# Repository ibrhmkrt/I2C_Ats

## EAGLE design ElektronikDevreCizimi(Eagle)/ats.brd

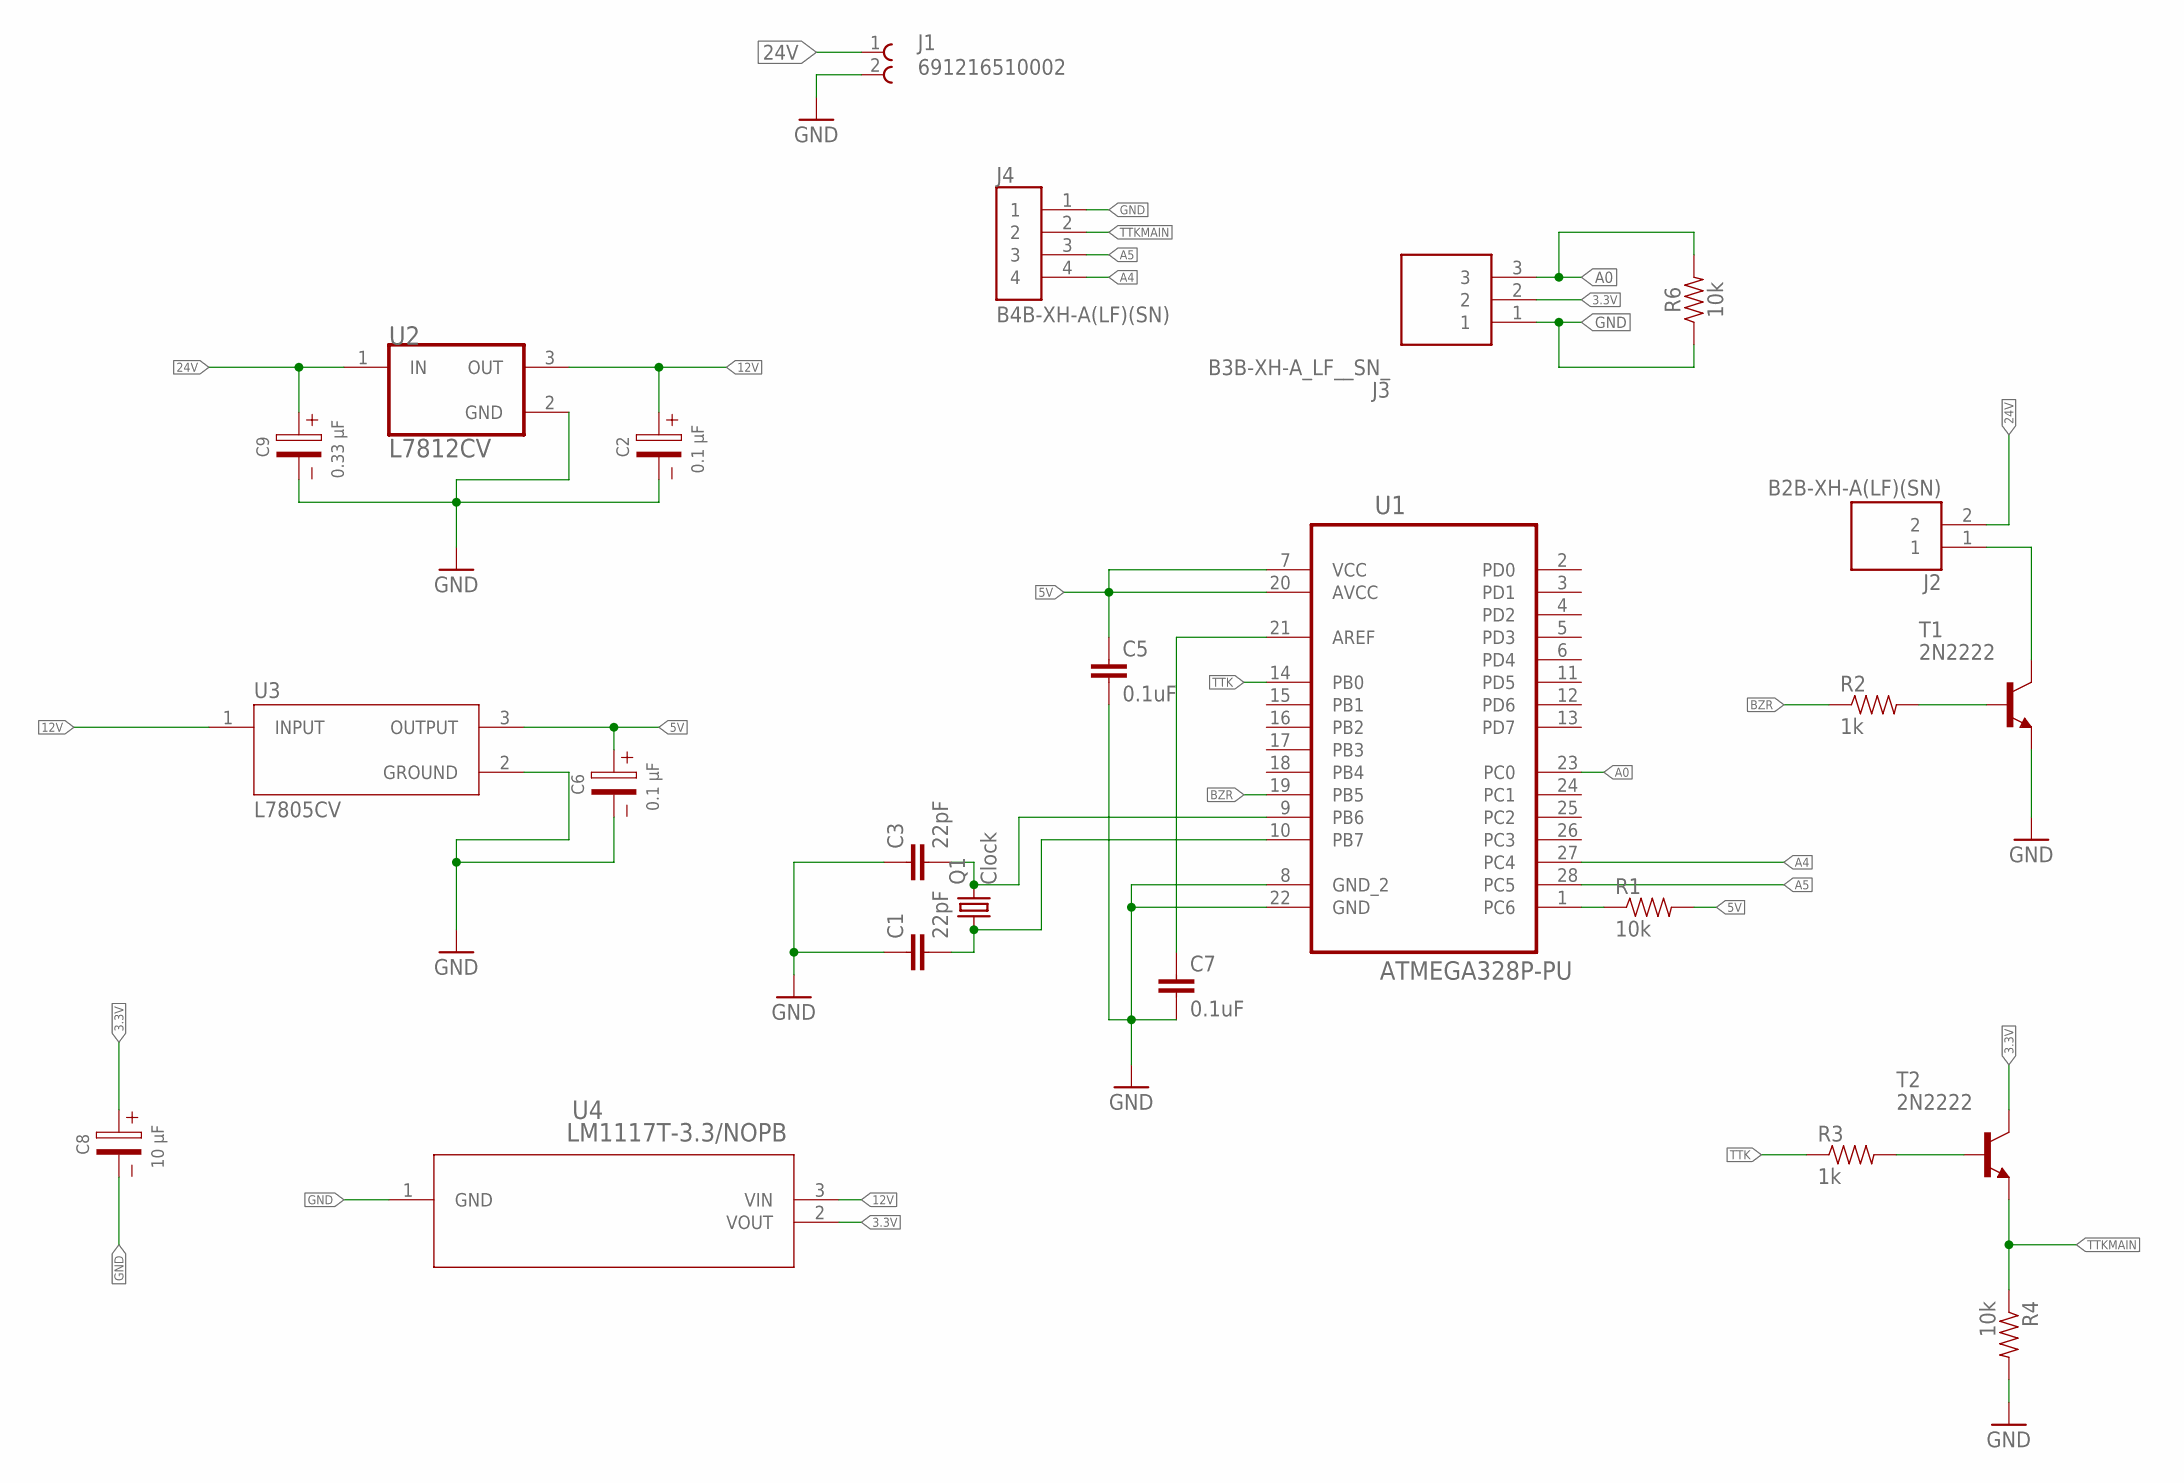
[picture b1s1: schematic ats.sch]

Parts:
C1, C3: 22pF; CAP-PTH-2.54
C2, C6: 0.1 µF; WCAP-ATG5_5X11(DXL)
C5, C7: 0.1uF; CAP-PTH-SMALL-KIT
C8: 10 µF; WCAP-ATG5_5X11(DXL)
C9: 0.33 µF; WCAP-ATG5_5X11(DXL)
J1: 691216510002
J2: B2B-XH-A(LF)(SN); JST_B2B-XH-A(LF)(SN)
J3: B3B-XH-A_LF__SN_; SHDR3W64P0X250_1X3_990X575X700
J4: B4B-XH-A(LF)(SN); JST_B4B-XH-A(LF)(SN)
Q1: Clock; HC49/S
R1, R4, R6: 10k; AXIAL-0.3
R2, R3: 1k; AXIAL-0.3
T1, T2: 2N2222; TO92-EBC-OVAL
U1: ATMEGA328P-PU; DIP254P762X457-28
U2: L7812CV; TO-220-3
U3: L7805CV; TO255P1040X460X1968-3
U4: LM1117T-3.3/NOPB; T03B_TEX

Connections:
3.3V: C8.1 (+), J3.2, T2.C, U4.2 (VOUT)
5V: C5.1, C6.1 (+), R1.P$2 (2), U1.7 (VCC), U1.20 (AVCC), U3.3 (OUTPUT)
12V: C2.1 (+), U2.3 (OUT), U3.1 (INPUT), U4.3 (VIN)
24V: C9.1 (+), J1.1, J2.2, U2.1 (IN)
A0: J3.3, R6.P$2 (2), U1.23 (PC0)
A4: J4.4, U1.27 (PC4)
A5: J4.3, U1.28 (PC5)
BZR: R2.P$1 (1), U1.19 (PB5)
GND: C1.1, C2.2 (-), C3.1, C5.2, C6.2 (-), C7.2, C8.2 (-), C9.2 (-), J1.2, J3.1, J4.1, R4.P$2 (2), R6.P$1 (1), T1.E, U1.8 (GND_2), U1.22 (GND), U2.2 (GND), U3.2 (GROUND), U4.1 (GND)
unnamed: R1.P$1 (1), U1.1 (PC6)
unnamed: J2.1, T1.C
unnamed: R2.P$2 (2), T1.B
unnamed: C3.2, Q1.2, U1.9 (PB6)
unnamed: C1.2, Q1.1, U1.10 (PB7)
unnamed: C7.1, U1.21 (AREF)
unnamed: R3.P$2 (2), T2.B
TTK: R3.P$1 (1), U1.14 (PB0)
TTKMAIN: J4.2, R4.P$1 (1), T2.E

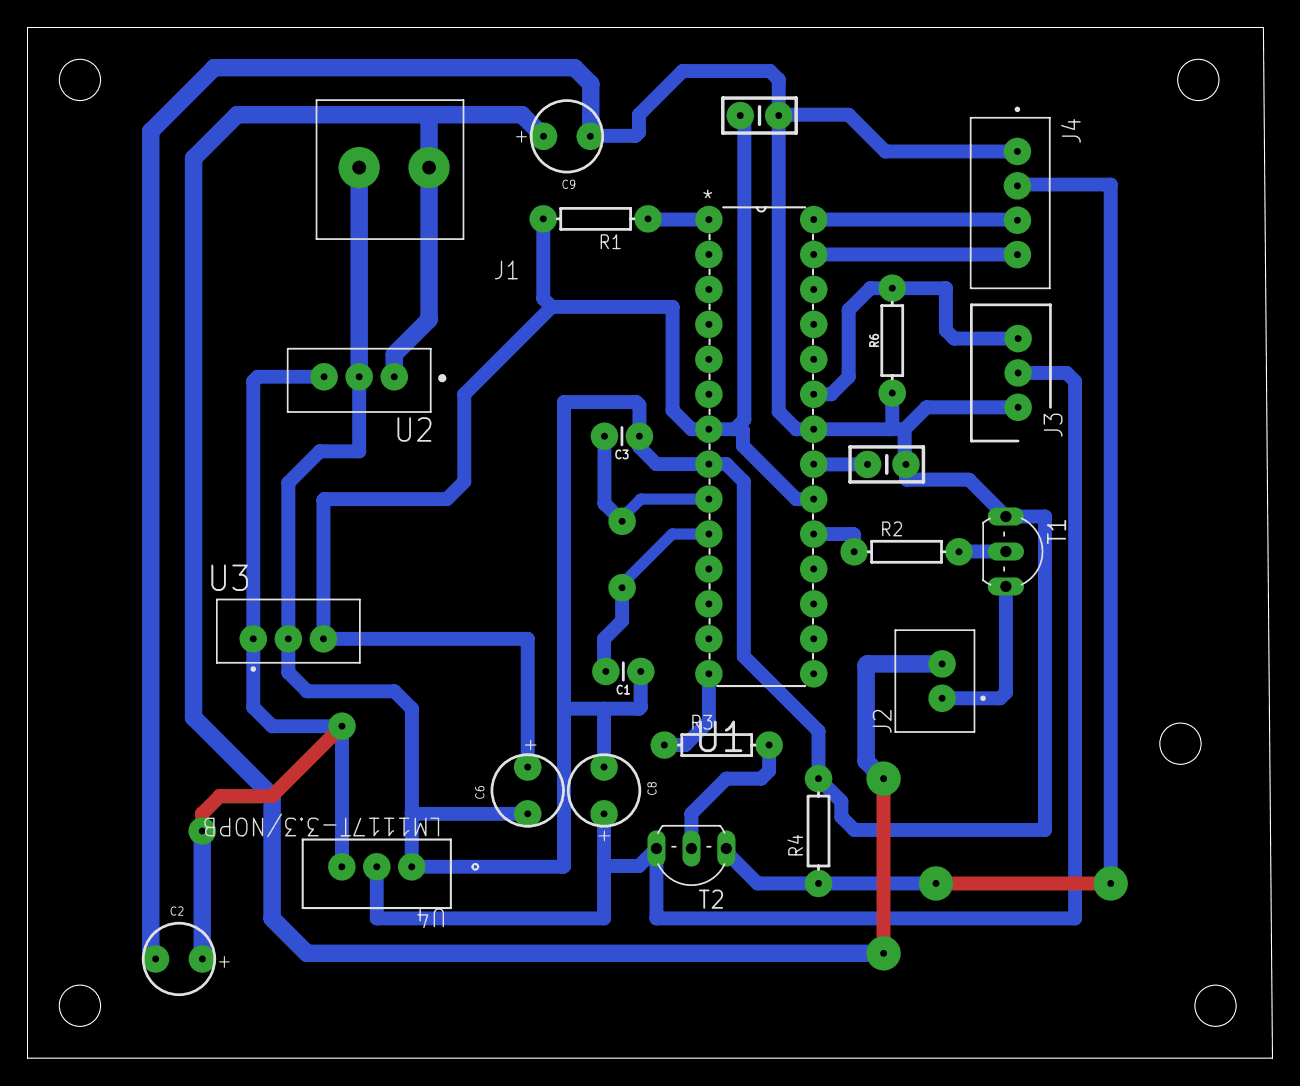
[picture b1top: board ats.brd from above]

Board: 2 copper layers, 90.5 x 74.9 mm, 24 parts (1 on the bottom side), 18 nets.

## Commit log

2020-02-20 I2C_Protocol_Ats
2020-02-20 Ats_I2C_Czm
2020-10-17 UpdatedAts

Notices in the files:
parts and their libraries:
Wurth_Capacitors_WCAP-ATG5-01uf-033uf: Copyright: Würth Elektronik
SparkFun-Resistors-10k: Licensing: Creative Commons ShareAlike 4.0 International - https://creativecommons.org/licenses/by-sa/4.0
COPYRIGHT: Copyright (C) 2018 Accelerated Designs. All rights reserved
